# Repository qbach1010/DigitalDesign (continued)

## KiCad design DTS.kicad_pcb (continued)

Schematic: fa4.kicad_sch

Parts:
U12, U16: 4081; CERDIP-14_W7.62mm_SideBrazed_LongPads_Socket
U14, U37: 4069; CERDIP-14_W7.62mm_SideBrazed_LongPads_Socket
U31: 4071; CERDIP-14_W7.62mm_SideBrazed_LongPads_Socket

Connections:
/Multiplier/A0B1: U12.6, U12.12, U14.1; also elsewhere on the board
/Multiplier/A1B0: U12.5, U12.8, U37.13; also elsewhere on the board
/Multiplier/FullAdder/(xy' + x'y)': U14.6, U16.8
/Multiplier/FullAdder/c_in': U14.4, U16.6
/Multiplier/FullAdder/temp1: U16.4, U31.5
/Multiplier/FullAdder/temp2: U16.10, U31.6
/Multiplier/FullAdder/temp3: U16.11, U31.9
/Multiplier/FullAdder/x': U12.13, U37.12
/Multiplier/FullAdder/x'y: U12.11, U31.2
/Multiplier/FullAdder/xy: U12.4, U31.8
/Multiplier/FullAdder/xy': U12.10, U31.1
/Multiplier/FullAdder/xy' + x'y: U14.5, U16.5, U16.12, U31.3
/Multiplier/FullAdder/y': U12.9, U14.2
/Multiplier/cout1: U31.10; also elsewhere on the board
/mult1: U31.4; also elsewhere on the board
GND: U14.3, U16.9, U16.13; also elsewhere on the board

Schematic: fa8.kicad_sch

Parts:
U5, U32: 4069; CERDIP-14_W7.62mm_SideBrazed_LongPads_Socket
U39, U42: 4081; CERDIP-14_W7.62mm_SideBrazed_LongPads_Socket
U43: 4071; CERDIP-14_W7.62mm_SideBrazed_LongPads_Socket

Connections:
/Multiplier/(A1B2)': U32.11, U39.6, U39.12; also elsewhere on the board
/Multiplier/FullAdder4/(xy' + x'y)': U5.2, U42.8
/Multiplier/FullAdder4/c_in': U32.12, U42.6
/Multiplier/FullAdder4/temp1: U42.4, U43.5
/Multiplier/FullAdder4/temp2: U42.10, U43.6
/Multiplier/FullAdder4/temp3: U42.11, U43.9
/Multiplier/FullAdder4/x': U32.8, U39.13
/Multiplier/FullAdder4/x'y: U39.11, U43.2
/Multiplier/FullAdder4/xy: U39.4, U43.8
/Multiplier/FullAdder4/xy': U39.10, U43.1
/Multiplier/FullAdder4/xy' + x'y: U5.1, U42.5, U42.12, U43.3
/Multiplier/FullAdder4/y': U32.10, U39.9
/Multiplier/cout4: U32.13, U42.9, U42.13; also elsewhere on the board
/Multiplier/cout5: U43.10; also elsewhere on the board
/Multiplier/sum2: U32.9, U39.5, U39.8; also elsewhere on the board
/mult3: U43.4; also elsewhere on the board

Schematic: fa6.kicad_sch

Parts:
U22: 4069; CERDIP-14_W7.62mm_SideBrazed_LongPads_Socket
U25, U30: 4081; CERDIP-14_W7.62mm_SideBrazed_LongPads_Socket
U36, U40: 4071; CERDIP-14_W7.62mm_SideBrazed_LongPads_Socket

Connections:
/Multiplier/(A2B1)': U22.3, U25.5, U25.8; also elsewhere on the board
/Multiplier/FullAdder2/(xy' + x'y)': U22.10, U30.8
/Multiplier/FullAdder2/c_in': U22.8, U30.6
/Multiplier/FullAdder2/temp1: U30.4, U36.8
/Multiplier/FullAdder2/temp2: U30.10, U36.9
/Multiplier/FullAdder2/temp3: U30.11, U36.13
/Multiplier/FullAdder2/x': U22.4, U25.13
/Multiplier/FullAdder2/x'y: U25.11, U40.2
/Multiplier/FullAdder2/xy: U25.4, U36.12
/Multiplier/FullAdder2/xy': U25.10, U40.1
/Multiplier/FullAdder2/xy' + x'y: U22.11, U30.5, U30.12, U40.3
/Multiplier/FullAdder2/y': U22.6, U25.9
/Multiplier/cout2: U22.9, U30.9, U30.13; also elsewhere on the board
/Multiplier/cout3: U36.11; also elsewhere on the board
/Multiplier/sum2: U36.10; also elsewhere on the board
VCC: U22.5, U25.6, U25.12; also elsewhere on the board

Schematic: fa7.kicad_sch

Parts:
U22, U32: 4069; CERDIP-14_W7.62mm_SideBrazed_LongPads_Socket
U30, U35, U39: 4081; CERDIP-14_W7.62mm_SideBrazed_LongPads_Socket
U40: 4071; CERDIP-14_W7.62mm_SideBrazed_LongPads_Socket

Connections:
/Multiplier/(A0B2)': U30.2, U32.1, U35.5; also elsewhere on the board
/Multiplier/FullAdder3/(xy' + x'y)': U32.6, U35.12
/Multiplier/FullAdder3/c_in': U32.4, U35.9
/Multiplier/FullAdder3/temp1: U35.10, U40.8
/Multiplier/FullAdder3/temp2: U35.11, U40.9
/Multiplier/FullAdder3/temp3: U39.3, U40.13
/Multiplier/FullAdder3/x': U22.12, U35.6
/Multiplier/FullAdder3/x'y: U35.4, U40.6
/Multiplier/FullAdder3/xy: U30.3, U40.12
/Multiplier/FullAdder3/xy': U35.3, U40.5
/Multiplier/FullAdder3/xy' + x'y: U32.5, U35.8, U39.1, U40.4
/Multiplier/FullAdder3/y': U32.2, U35.2
/Multiplier/cout4: U40.11; also elsewhere on the board
/Multiplier/sum1: U22.13, U30.1, U35.1; also elsewhere on the board
/mult2: U40.10; also elsewhere on the board
GND: U32.3, U35.13, U39.2; also elsewhere on the board

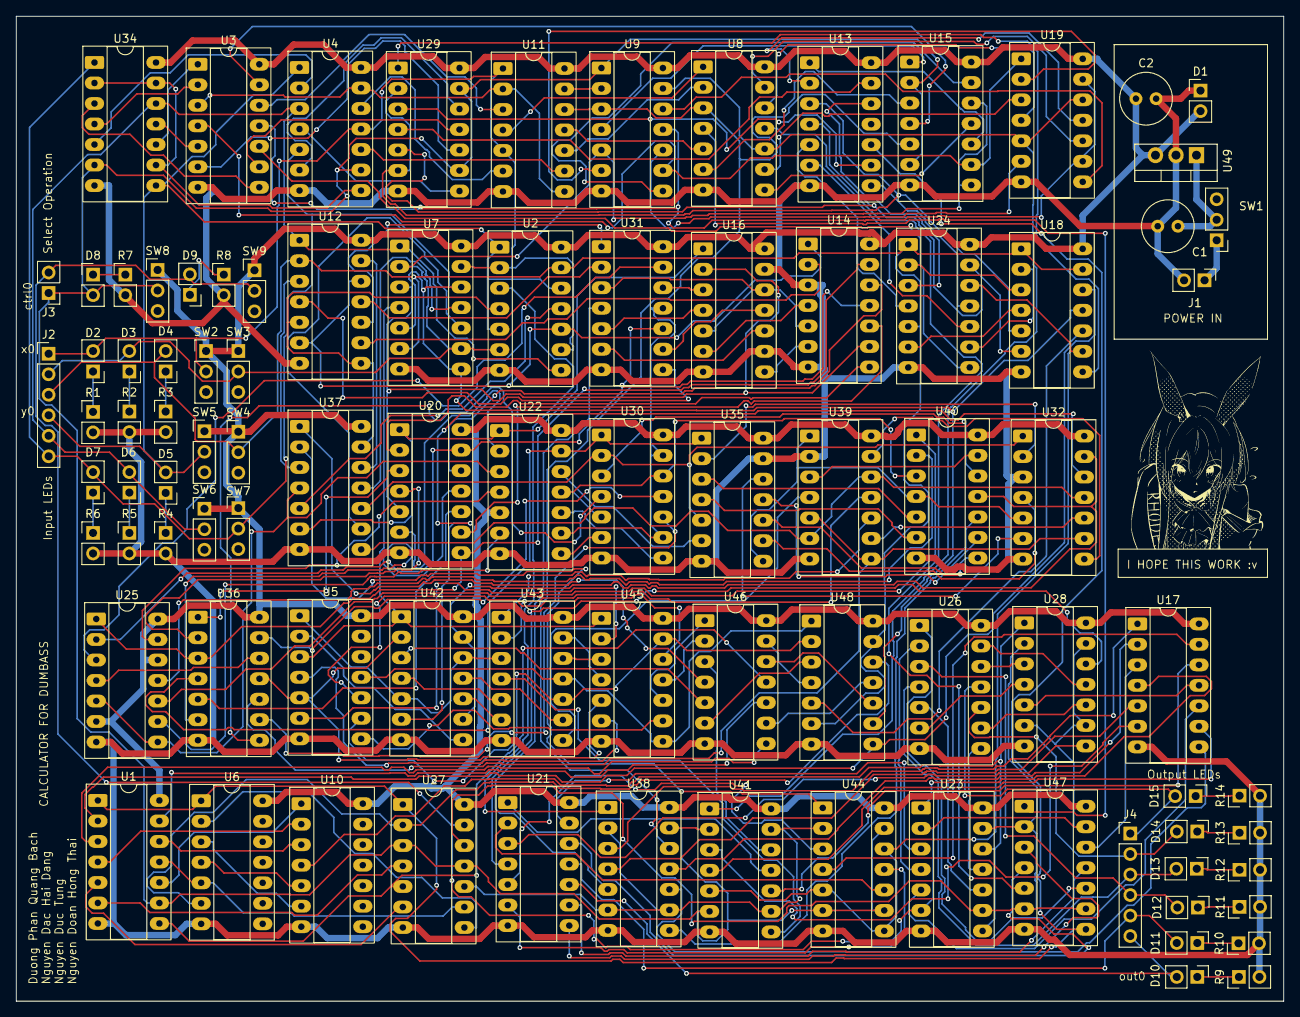
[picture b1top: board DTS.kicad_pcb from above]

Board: 2 copper layers, 157.0 x 122.0 mm, 92 parts (0 on the bottom side), 226 nets.

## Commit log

2026-04-05 README.md
2026-04-08 Add files via upload
    Added 3 bits 2:1 and 6 bits 4:1 multiplexer
    Added minus operation
2026-04-12 Add files via upload
    Waiting for approval
2026-05-01 Delete DTS.kicad_pcb
    remove the original pcb design
2026-05-01 Add files via upload
    This is my new pcb design file, please review
2026-05-01 Delete DTS.kicad_pcb
    this is the "hasnt fixxed" file
